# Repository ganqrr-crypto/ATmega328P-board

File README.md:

It's a custom microcontroller i will use for deveopment...

it features a Dc Power Jack Input supporting between 7 and 12v then it regulates to 5v and from 5v to 3.3..

it's built around ATmega328P microcontroller 

Schematics:

still in development but i am working on it these are first hours and that image above it's just the microcontroller schematic
i'll update whit more later

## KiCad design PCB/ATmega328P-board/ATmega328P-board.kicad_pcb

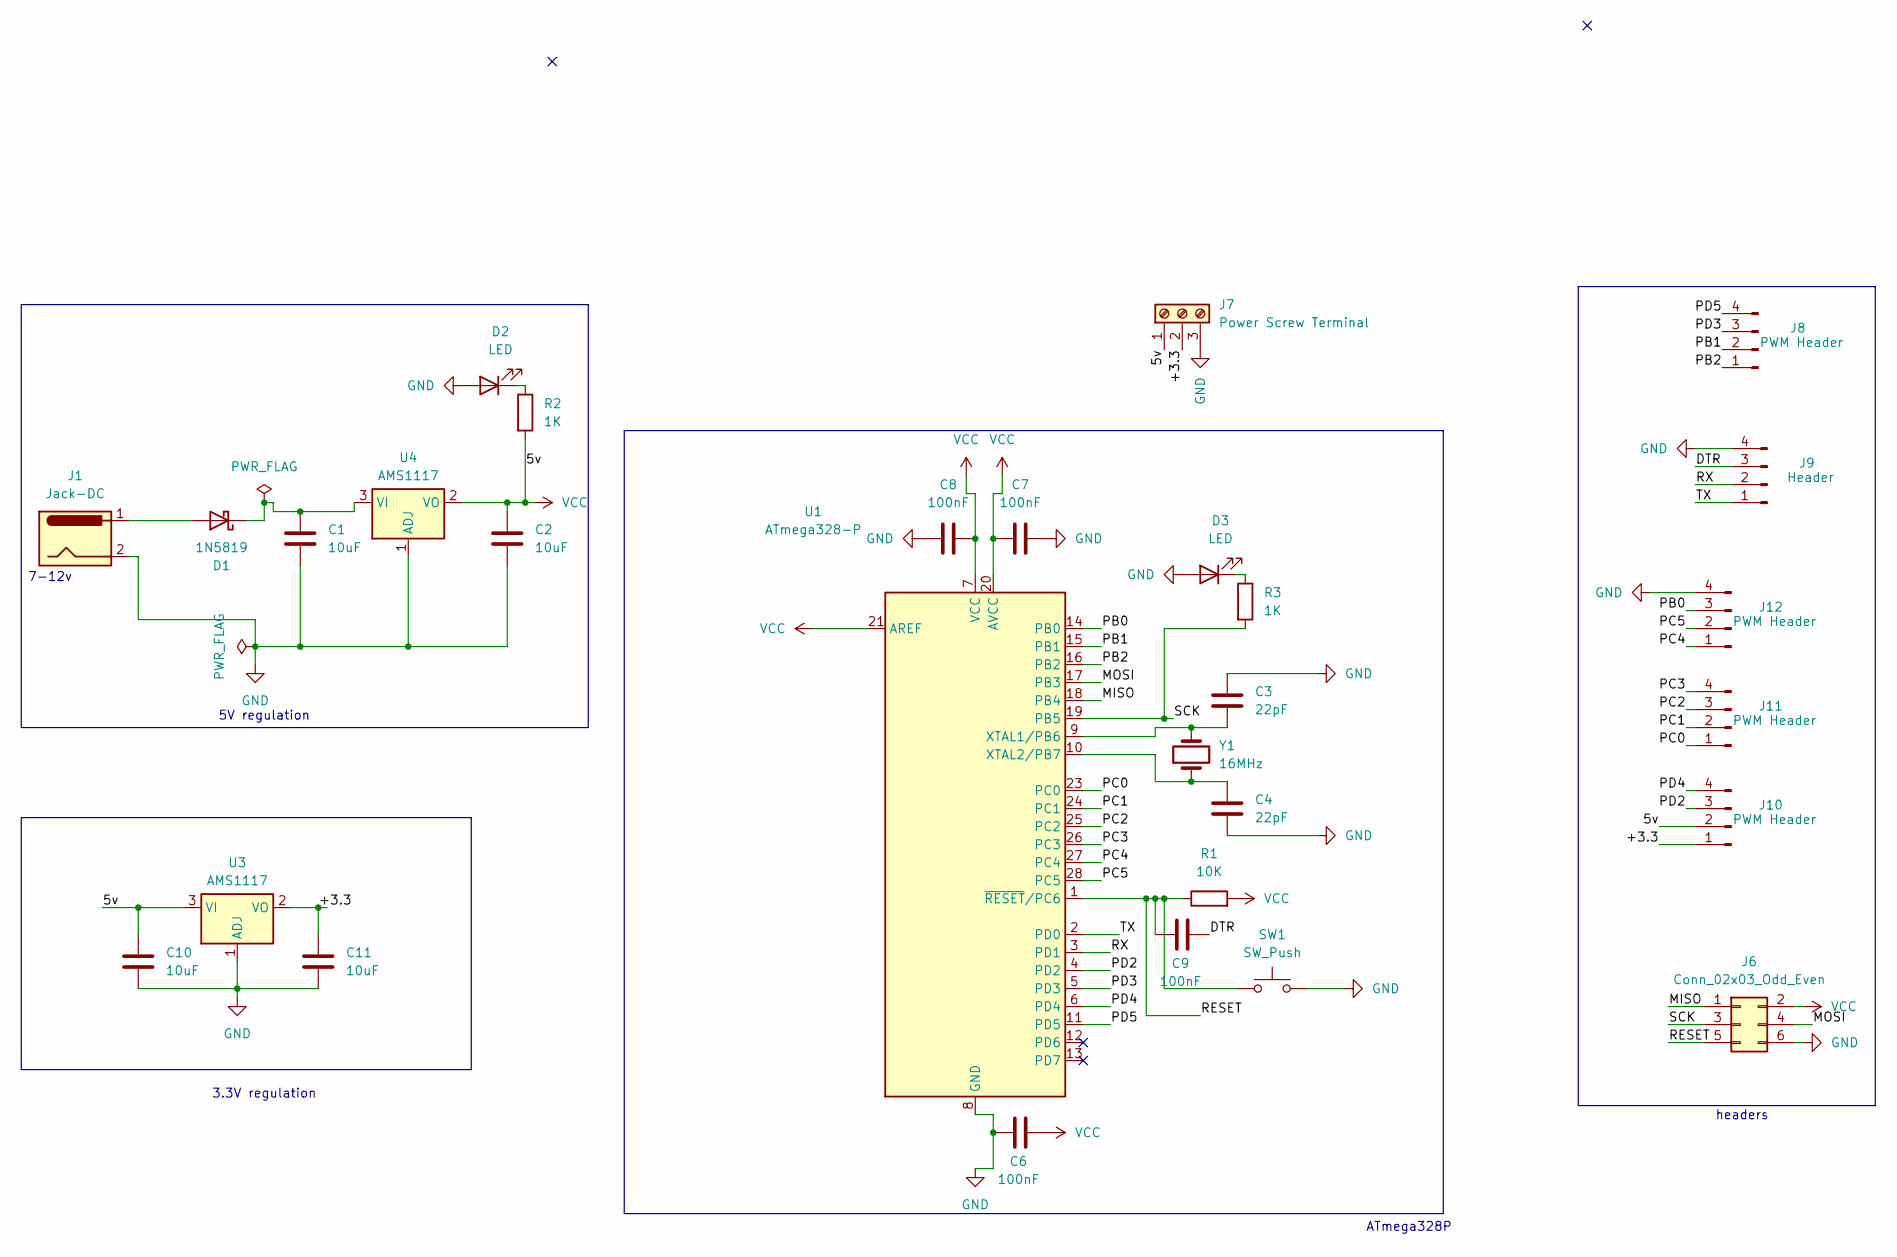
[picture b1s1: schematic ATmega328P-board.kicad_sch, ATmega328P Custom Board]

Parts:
C1: 10uF; CP_Radial_D5.0mm_P2.50mm
C2, C10, C11: 10uF; CP_Radial_D5.0mm_P2.00mm
C3, C4: 22pF; C_0805_2012Metric
C6, C7, C8, C9: 100nF; C_0805_2012Metric
D1: 1N5819; D_DO-41_SOD81_P10.16mm_Horizontal
D2, D3: LED; LED_D3.0mm
J1: Jack-DC; BarrelJack_Horizontal
J6: Conn_02x03_Odd_Even; PinHeader_2x03_P2.54mm_Vertical
J7: Power Screw Terminal; Altech_AK100_1x03_P5.00mm
J8, J10, J11, J12: PWM Header; PinHeader_1x04_P2.54mm_Vertical
J9: Header; PinHeader_1x04_P2.54mm_Vertical
R1: 10K; R_0805_2012Metric
R2, R3: 1K; R_0805_2012Metric
SW1: SW_Push; SW_PUSH_6mm
U1: ATmega328-P; DIP-28_W7.62mm
U3, U4: AMS1117; SOT-223-3_TabPin2
Y1: 16MHz; Crystal_HC49-4H_Vertical

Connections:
/+3.3: C11.1, J7.2, J10.1, U3.2 (VO)
/DTR: C9.1, J9.3
/MISO: J6.1, U1.18 (PB4)
/MOSI: J6.4, U1.17 (PB3)
/PB0: J12.3, U1.14 (PB0)
/PB1: J8.2, U1.15 (PB1)
/PB2: J8.1, U1.16 (PB2)
/PC0: J11.1, U1.23 (PC0)
/PC1: J11.2, U1.24 (PC1)
/PC2: J11.3, U1.25 (PC2)
/PC3: J11.4, U1.26 (PC3)
/PC4: J12.1, U1.27 (PC4)
/PC5: J12.2, U1.28 (PC5)
/PD2: J10.3, U1.4 (PD2)
/PD3: J8.3, U1.5 (PD3)
/PD4: J10.4, U1.6 (PD4)
/PD5: J8.4, U1.11 (PD5)
/RESET: C9.2, J6.5, R1.1, SW1.1, U1.1 (~RESET/PC6)
/RX: J9.2, U1.3 (PD1)
/SCK: J6.3, R3.2, U1.19 (PB5)
/TX: J9.1, U1.2 (PD0)
GND: C1.2, C2.2, C3.1, C4.2, C6.2, C7.2, C8.2, C10.2, C11.2, D2.2 (A), D3.2 (A), J1.2, J6.6, J7.3, J9.4, J12.4, SW1.2, U1.8 (GND), U1.22 (GND), U3.1 (ADJ), U4.1 (ADJ)
unnamed: D1.2 (A), J1.1
unnamed: C1.1, D1.1 (K), U4.3 (VI)
unnamed: D2.1 (K), R2.1
unnamed: D3.1 (K), R3.1
unnamed: C3.2, U1.9 (XTAL1/PB6), Y1.2
unnamed: C4.1, U1.10 (XTAL2/PB7), Y1.1
VCC: C2.1, C6.1, C7.1, C8.1, C10.1, J6.2, J7.1, J10.2, R1.2, R2.2, U1.7 (VCC), U1.20 (AVCC), U1.21 (AREF), U3.3 (VI), U4.2 (VO)

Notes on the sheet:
ATmega328P
5V regulation
7-12v
3.3V regulation
headers

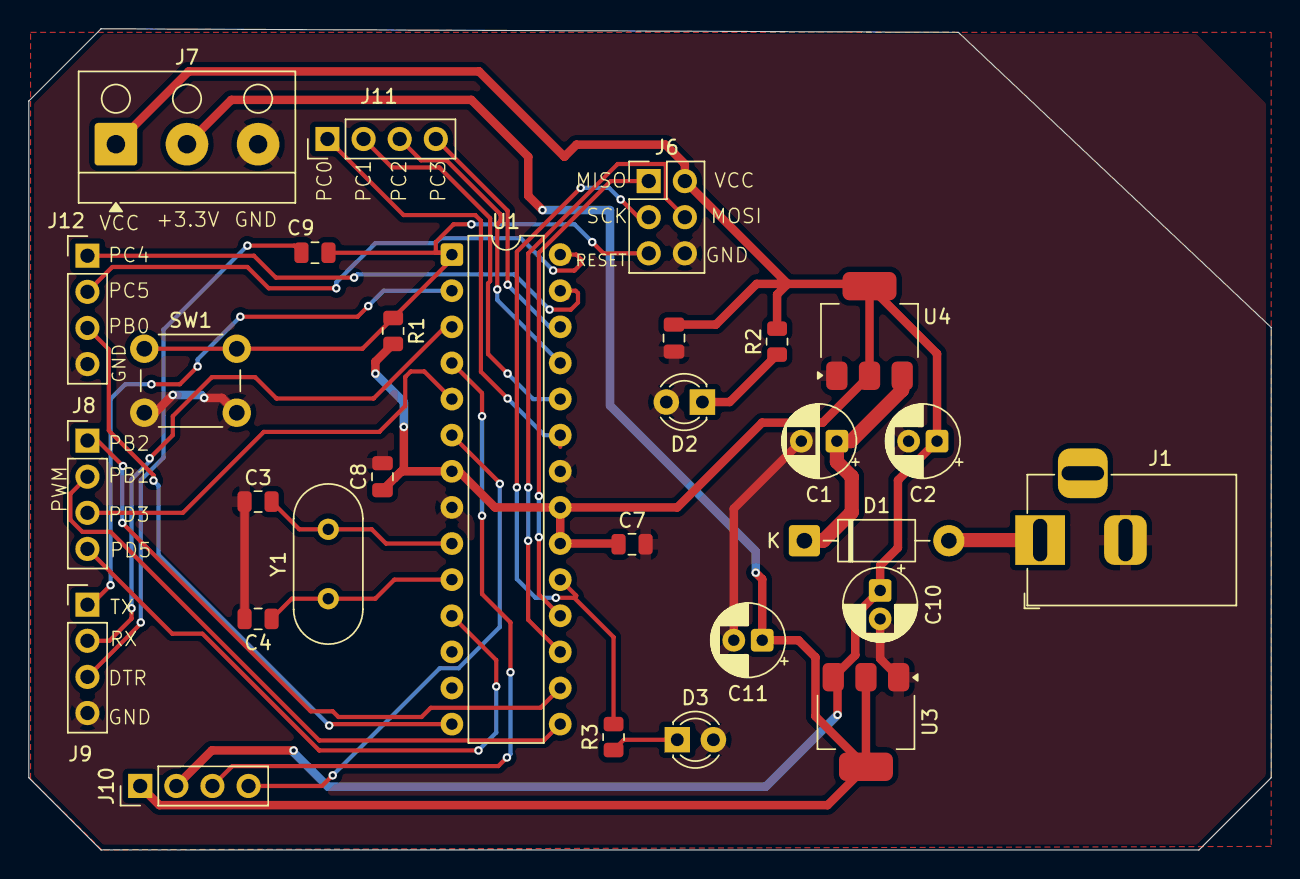
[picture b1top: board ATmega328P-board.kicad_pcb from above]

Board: 2 copper layers, 87.4 x 57.8 mm, 29 parts (0 on the bottom side), 29 nets.

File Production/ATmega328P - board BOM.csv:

Reference,Qty,Value,,Footprint,,,,,Part Number,,Link,,,,,Cost
C1,1,10uF,,Capacitor_THT:CP_Radial_D5.0mm_P2.50mm,,,,,C2841113,,https://www.lcsc.com/it/product-detail/C2841113.html,,,,,0.95€
"C2,C10,C11",3,10uF,,Capacitor_THT:CP_Radial_D5.0mm_P2.50mm,,,,,C2841113,,https://www.lcsc.com/it/product-detail/C2841113.html,,,,,0.95€
"C3,C4",2,22pF,,Capacitor_SMD:C_0805_2012Metric,,,,,C1804,,https://www.lcsc.com/it/product-detail/C1804.html,,,,,0.55€
"C6,C7,C8,C9",4,100nF,,Capacitor_SMD:C_0805_2012Metric,,,,,C49678,,https://www.lcsc.com/it/product-detail/C49678.html,,,,,0.34€
D1,1,1N5819,,Diode_THT:D_DO-41_SOD81_P10.16mm_Horizontal,,,,,C2474,,https://www.lcsc.com/it/product-detail/C2474.html,,,,,
,,,,,,,,,,,,,,,,
J1,1,Jack-DC,,Connector_BarrelJack:BarrelJack_Horizontal,,,,,C194407,,https://www.lcsc.com/it/product-detail/C194407.html,,,,,0.54€
J6,1,Conn_02x03_Odd_Even,,Connector_PinHeader_2.54mm:PinHeader_2x03_P2.54mm_Vertical,,,,,C65114,,https://www.lcsc.com/it/product-detail/C65114.html,,,,,0.40€
J7,1,Power Screw Terminal,,TerminalBlock_Altech:Altech_AK100_1x03_P5.00mm,,,,,C474901,,https://www.lcsc.com/it/product-detail/C474901.html,,,,,0.63€
J8,4,PWM Header,,Connector_PinHeader_2.54mm:PinHeader_1x04_P2.54mm_Vertical,,,,,C5116483,,https://www.lcsc.com/it/product-detail/C5116483.html,,,,,0.40€
"J9,J10,J11,J1",1,Header,,Connector_PinHeader_2.54mm:PinHeader_1x04_P2.54mm_Vertical,,,,,C5116483,,https://www.lcsc.com/it/product-detail/C5116483.html,,,,,0.40€
R1,1,10K,,Resistor_SMD:R_0805_2012Metric,,,,,C2907219,,https://www.lcsc.com/it/product-detail/C2907219.html,,,,,0.31€
"R2,R3",2,1K,,Resistor_SMD:R_0805_2012Metric,,,,,C3016664,,https://www.lcsc.com/it/product-detail/C3016664.html,,,,,0.17€
SW1,1,SW_Push,,Button_Switch_THT:SW_PUSH_6mm,,,,,C36938886,,https://www.lcsc.com/it/product-detail/C36938886.html,,,,,0.86€
U1,1,ATmega328-P,,Package_DIP:DIP-28_W7.62mm,,,,,C33901,,https://www.lcsc.com/it/product-detail/C33901.html,,,,,2.33€
U3,1,AMS1117,,Package_TO_SOT_SMD:SOT-223-3_TabPin2,,,,,C6186,,https://www.lcsc.com/it/product-detail/C6186.html,,,,,1.14€
Y1,1,16MHz,,Crystal:Crystal_HC49-4H_Vertical,,,,,C16212,,https://www.lcsc.com/it/product-detail/C16212.html,,,,,0.40€
U4,1,AMS1117,,Package_TO_SOT_SMD:SOT-223-3_TabPin2,,,,,C6187,,https://www.lcsc.com/it/product-detail/C6187.html,,,,,0.93€
